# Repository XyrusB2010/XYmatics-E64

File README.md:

# XYmatics E64
XYmatics E64 (Engine, 64-bit) is a 5-axis Klipper mainboard, powered by a Raspberry Pi CM4 and STM32F407. It was originally built for <a href='https://github.com/XyrusB2010/XYmatics-Alpha/tree/main'>XYmatics Alpha</a>, but you can also use it for most 3D Printers.

## E64 Features
- Powered by STM32F407VET6 (MCU) and Raspberry Pi CM4 (Host)
- 1 USB-micro OTG port + 2 USB-A ports + 1 USB JST breakout, 100 Mbit RJ45 Socket for LAN, Micro SD card for extra storage
- 5 TMC2209 Stepsticks to drive stepper motors
- 3 Endstops/Switches
- 5 Controllable fans on base board + 1 for Raspberry Pi
- 8 CAN FD bus ports to reduce amount of cables
- CSI for camera input
- HDMI or DSI for display output
- I2C bus broken out

## E64 PCB

# XYmatics X42
XYmatics X42 (Xpansion, for 42mm motors) is a Klipper expansion board, designed to mount onto 42mm stepper motors. Powered by a STM32G0B1, it communicates to the E64 mainboard through CAN FD. This board simplifies the mainboard, and reduces the amount of cables going out. The X42 can also be used with most other 3D Printers.

## X42 Features
- Powered by STM32G0B1CBT6
- Supports Laser engravers, CNC routers and FDM extruders
- TJA1051T CAN FD module to communicate with E64
- ~~BLTouch compatible~~
- Two PWM controllable fans
- ADXL345 accelerometer included
- ~~3~~ 1 Endstop/Switch
- I2C bus ~~and neopixel~~ broken out
>  [!NOTE]
>  May re-add these removed features in future if possible.

## X42 PCB

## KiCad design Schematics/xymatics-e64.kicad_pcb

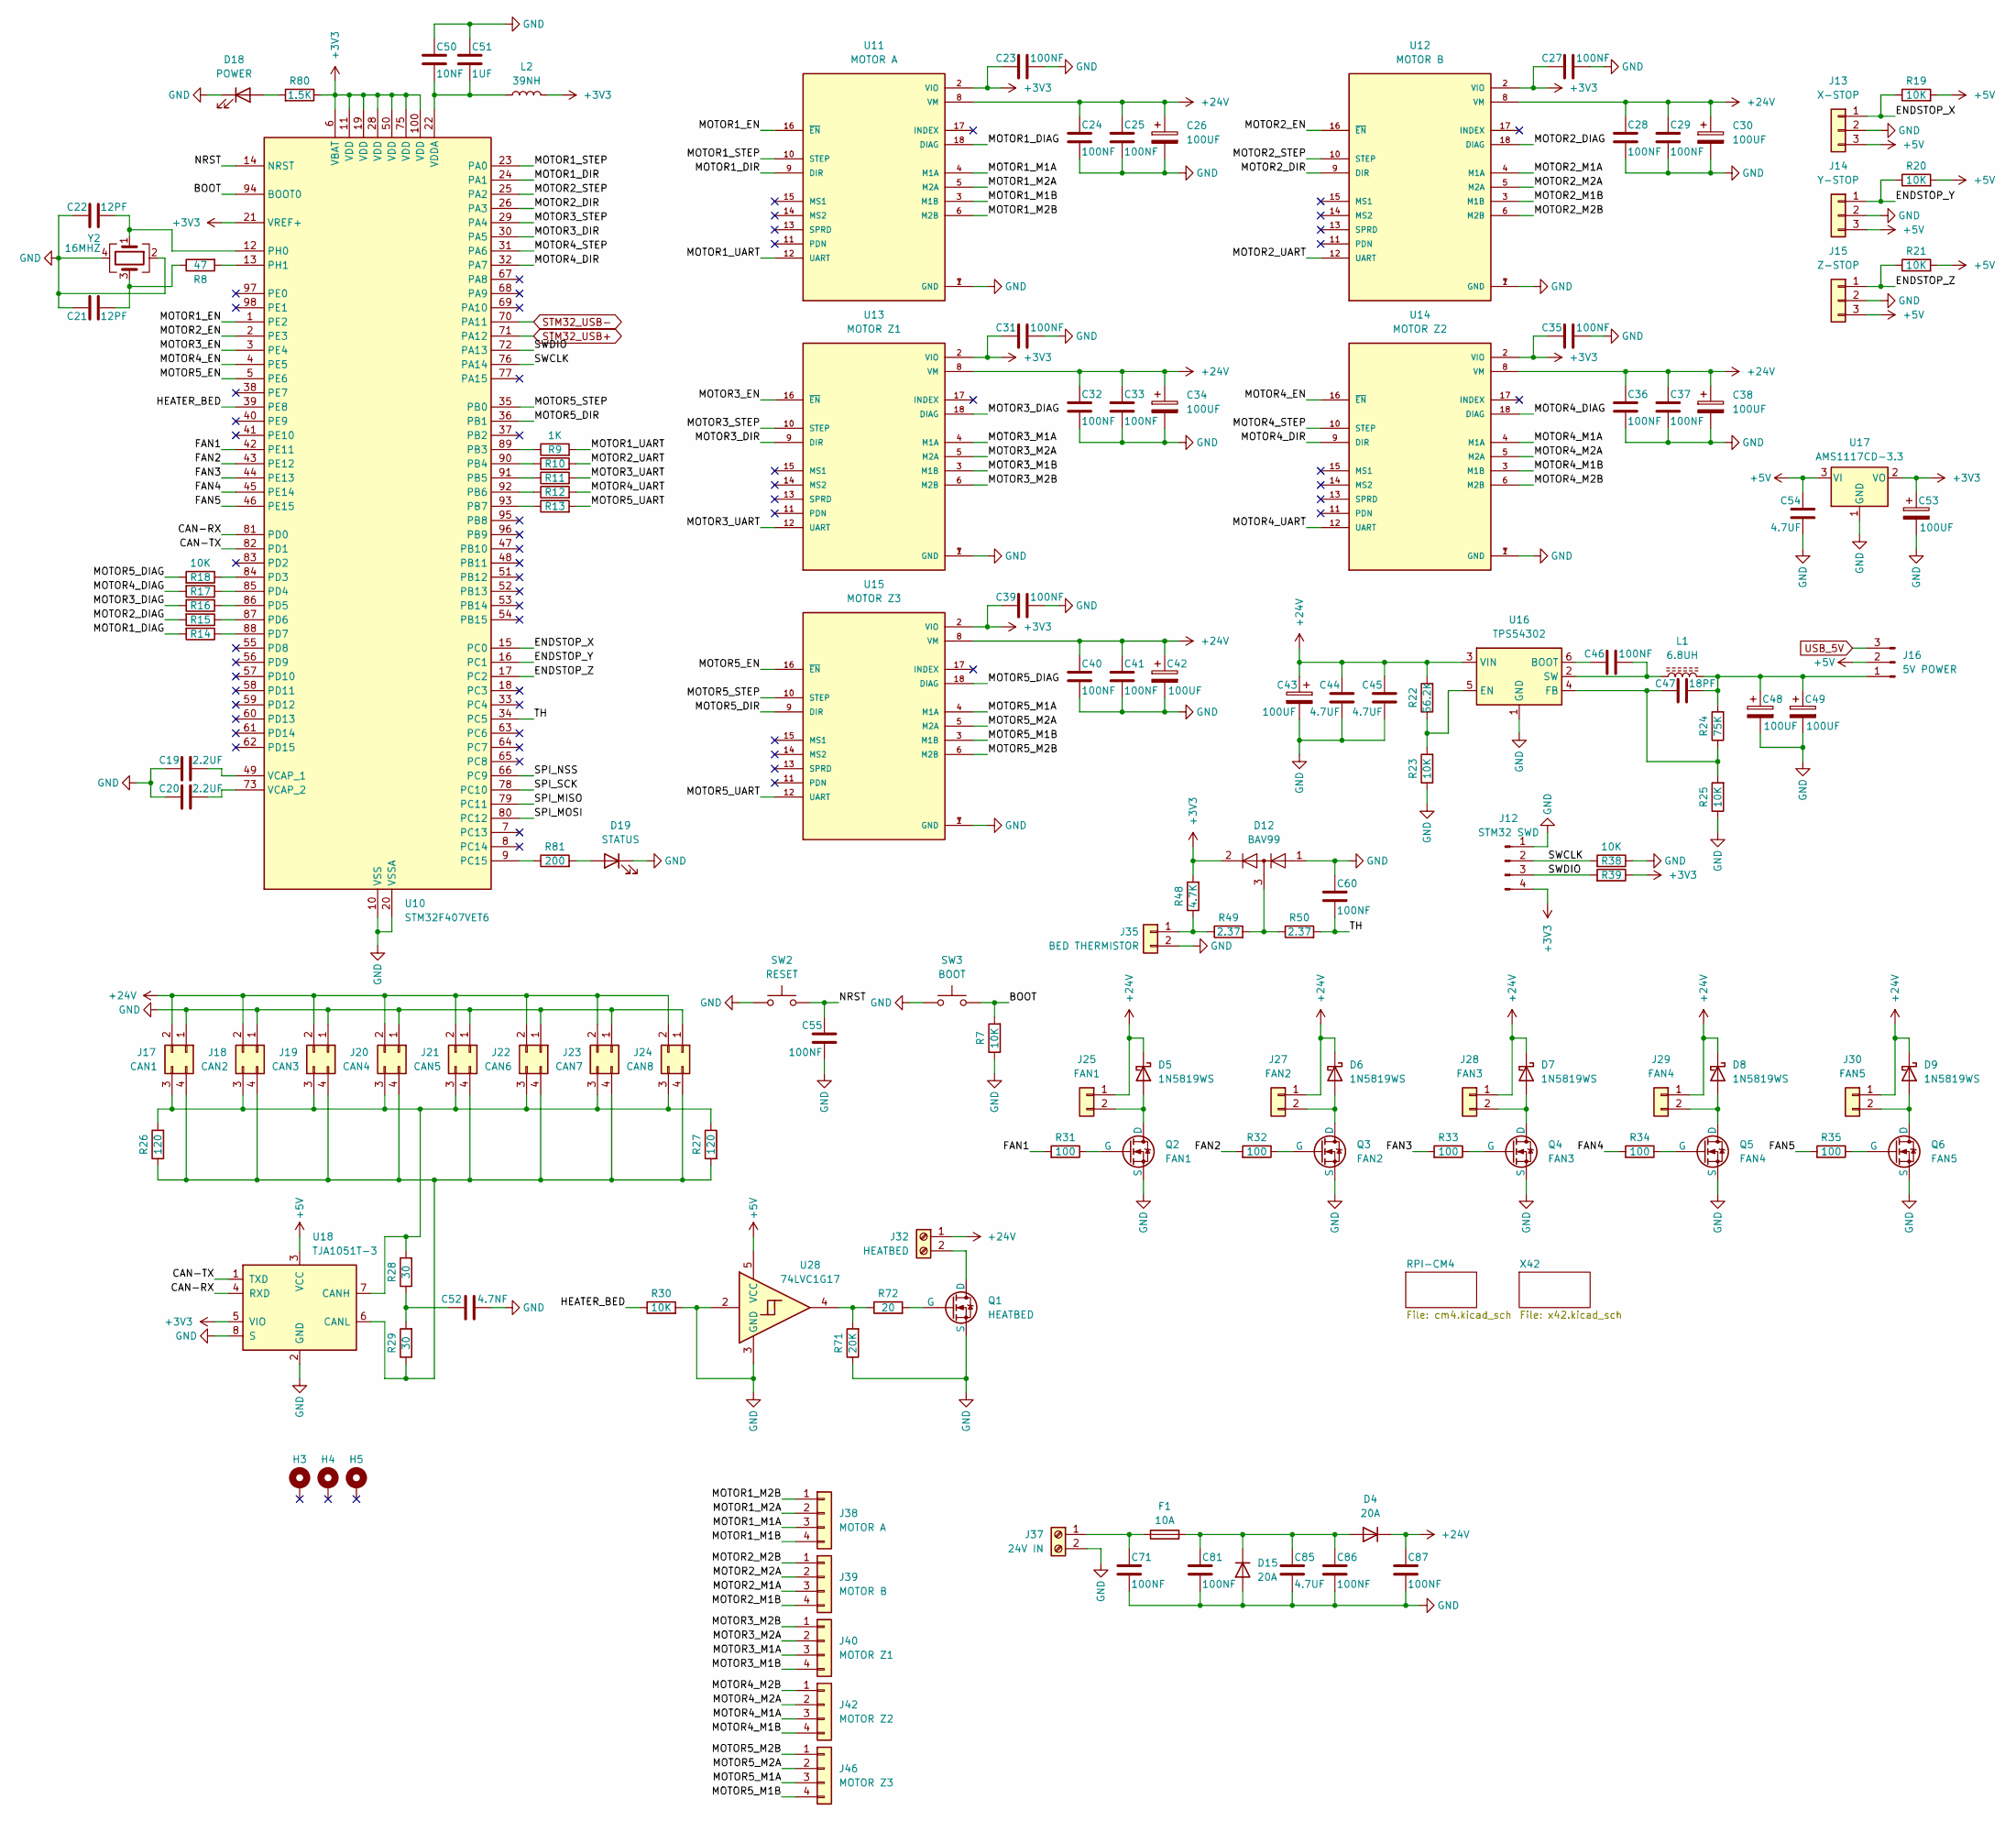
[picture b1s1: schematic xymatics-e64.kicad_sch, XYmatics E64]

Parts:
C19, C20: 2.2UF; C_0805_2012Metric
C21, C22: 12PF; C_0805_2012Metric
C23, C24, C25, C27, C28, C29, C31, C32, C33, C35, C36, C37, C39, C40, C41, C46, C55, C60, C71, C81, C86, C87: 100NF; C_0805_2012Metric
C26, C30, C34, C38, C42, C43, C48, C49, C53: 100UF; CP_Elec_5x3
C44, C45, C54, C85: 4.7UF; C_0805_2012Metric
C47: 18PF; C_0805_2012Metric
C50: 10NF; C_0805_2012Metric
C51: 1UF; C_0805_2012Metric
C52: 4.7NF; C_0805_2012Metric
D4, D15: 20A; D_SMB
D5, D6, D7, D8, D9: 1N5819WS; D_SOD-323
D12: BAV99; SOT-23
D18: POWER; LED_0805_2012Metric
D19: STATUS; LED_0805_2012Metric
F1: 10A; Fuse_Blade_ATO_directSolder
H3, H4, H5: MountingHole_Pad; MountingHole_3mm_Pad
J12: STM32 SWD; PinHeader_1x04_P2.54mm_Vertical
J13: X-STOP; JST_XH_B3B-XH-A_1x03_P2.50mm_Vertical
J14: Y-STOP; JST_XH_B3B-XH-A_1x03_P2.50mm_Vertical
J15: Z-STOP; JST_XH_B3B-XH-A_1x03_P2.50mm_Vertical
J16: 5V POWER; PinHeader_1x03_P2.54mm_Vertical
J17: CAN1; Molex_Micro-Fit_3.0_43045-0412_2x02_P3.00mm_Vertical
J18: CAN2; Molex_Micro-Fit_3.0_43045-0412_2x02_P3.00mm_Vertical
J19: CAN3; Molex_Micro-Fit_3.0_43045-0412_2x02_P3.00mm_Vertical
J20: CAN4; Molex_Micro-Fit_3.0_43045-0412_2x02_P3.00mm_Vertical
J21: CAN5; Molex_Micro-Fit_3.0_43045-0412_2x02_P3.00mm_Vertical
J22: CAN6; Molex_Micro-Fit_3.0_43045-0412_2x02_P3.00mm_Vertical
J23: CAN7; Molex_Micro-Fit_3.0_43045-0412_2x02_P3.00mm_Vertical
J24: CAN8; Molex_Micro-Fit_3.0_43045-0412_2x02_P3.00mm_Vertical
J25: FAN1; JST_XH_B2B-XH-A_1x02_P2.50mm_Vertical
J27: FAN2; JST_XH_B2B-XH-A_1x02_P2.50mm_Vertical
J28: FAN3; JST_XH_B2B-XH-A_1x02_P2.50mm_Vertical
J29: FAN4; JST_XH_B2B-XH-A_1x02_P2.50mm_Vertical
J30: FAN5; JST_XH_B2B-XH-A_1x02_P2.50mm_Vertical
J32: HEATBED; TerminalBlock_MaiXu_MX126-5.0-02P_1x02_P5.00mm
J35: BED THERMISTOR; JST_XH_B2B-XH-A_1x02_P2.50mm_Vertical
J37: 24V IN; TerminalBlock_MaiXu_MX126-5.0-02P_1x02_P5.00mm
J38: MOTOR A; JST_XH_B4B-XH-A_1x04_P2.50mm_Vertical
J39: MOTOR B; JST_XH_B4B-XH-A_1x04_P2.50mm_Vertical
J40: MOTOR Z1; JST_XH_B4B-XH-A_1x04_P2.50mm_Vertical
J42: MOTOR Z2; JST_XH_B4B-XH-A_1x04_P2.50mm_Vertical
J46: MOTOR Z3; JST_XH_B4B-XH-A_1x04_P2.50mm_Vertical
L1: 6.8UH; L_6.3x6.3_H3
L2: 39NH; L_0805_2012Metric
Q1: HEATBED; TO-252-2
Q2: FAN1; SOT-23
Q3: FAN2; SOT-23
Q4: FAN3; SOT-23
Q5: FAN4; SOT-23
Q6: FAN5; SOT-23
R7, R14, R15, R16, R17, R18, R19, R20, R21, R23, R25, R30, R38, R39: 10K; R_0805_2012Metric
R8: 47; R_0805_2012Metric
R9, R10, R11, R12, R13: 1K; R_0805_2012Metric
R22: 56.2K; R_1206_3216Metric
R24: 75K; R_1206_3216Metric
R26, R27: 120; R_0805_2012Metric
R28, R29: 30; R_0805_2012Metric
R31, R32, R33, R34, R35: 100; R_0805_2012Metric
R48: 4.7K; R_0805_2012Metric
R49, R50: 2.37; R_0805_2012Metric
R71: 20K; R_0805_2012Metric
R72: 20; R_0805_2012Metric
R80: 1.5K; R_0805_2012Metric
R81: 200; R_0805_2012Metric
SW2: RESET; SW_Tactile_SPST_NO_Straight_CK_PTS636Sx25SMTRLFS
SW3: BOOT; SW_Tactile_SPST_NO_Straight_CK_PTS636Sx25SMTRLFS
U10: STM32F407VET6; LQFP-100_14x14mm_P0.5mm
U11: MOTOR A; MODULE_TMC2209_SILENTSTEPSTICK; PARTREV 1.20
U12: MOTOR B; MODULE_TMC2209_SILENTSTEPSTICK; PARTREV 1.20
U13: MOTOR Z1; MODULE_TMC2209_SILENTSTEPSTICK; PARTREV 1.20
U14: MOTOR Z2; MODULE_TMC2209_SILENTSTEPSTICK; PARTREV 1.20
U15: MOTOR Z3; MODULE_TMC2209_SILENTSTEPSTICK; PARTREV 1.20
U16: TPS54302; SOT-23-6
U17: AMS1117CD-3.3; TO-252-2
U18: TJA1051T-3; SOIC-8_3.9x4.9mm_P1.27mm
U28: 74LVC1G17; SOT-23-5
Y2: 16MHZ; Crystal_SMD_Abracon_ABM3B-4Pin_5.0x3.2mm

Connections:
+3V3: C23.2, C27.2, C31.2, C35.2, C39.2, C53.1, D12.2 (A), J12.4, L2.2, R39.1, R48.2, R80.1, U10.6 (VBAT), U10.11 (VDD), U10.19 (VDD), U10.21 (VREF+), U10.28 (VDD), U10.50 (VDD), U10.75 (VDD), U10.100 (VDD), U11.2 (VIO), U12.2 (VIO), U13.2 (VIO), U14.2 (VIO), U15.2 (VIO), U17.2 (VO), U18.5 (VIO)
+5V: C54.1, J13.3, J14.3, J15.3, J16.2, R19.2, R20.2, R21.2, U17.3 (VI), U18.3 (VCC), U28.5 (VCC); also elsewhere on the board
+24V: C24.1, C25.1, C26.1, C28.1, C29.1, C30.1, C32.1, C33.1, C34.1, C36.1, C37.1, C38.1, C40.1, C41.1, C42.1, C43.1, C44.1, C45.1, C87.1, D4.1 (K), D5.1 (K), D6.1 (K), D7.1 (K), D8.1 (K), D9.1 (K), J17.2, J18.2, J19.2, J20.2, J21.2, J22.2, J23.2, J24.2, J25.1, J27.1, J28.1, J29.1, J30.1, J32.1, R22.2, U11.8 (VM), U12.8 (VM), U13.8 (VM), U14.8 (VM), U15.8 (VM), U16.3 (VIN)
/BOOT: R7.2, SW3.2, U10.94 (BOOT0)
/CAN-RX: U10.81 (PD0), U18.4 (RXD)
/CAN-TX: U10.82 (PD1), U18.1 (TXD)
/ENDSTOP_X: J13.1, R19.1, U10.15 (PC0)
/ENDSTOP_Y: J14.1, R20.1, U10.16 (PC1)
/ENDSTOP_Z: J15.1, R21.1, U10.17 (PC2)
/FAN1: R31.2, U10.42 (PE11)
/FAN2: R32.2, U10.43 (PE12)
/FAN3: R33.2, U10.44 (PE13)
/FAN4: R34.2, U10.45 (PE14)
/FAN5: R35.2, U10.46 (PE15)
/HEATER_BED: R30.1, U10.39 (PE8)
/MOTOR1_DIAG: R14.2, U11.18 (DIAG)
/MOTOR1_DIR: U10.24 (PA1), U11.9 (DIR)
/MOTOR1_EN: U10.1 (PE2), U11.16 (~EN)
/MOTOR1_M1A: J38.3, U11.4 (M1A)
/MOTOR1_M1B: J38.4, U11.3 (M1B)
/MOTOR1_M2A: J38.2, U11.5 (M2A)
/MOTOR1_M2B: J38.1, U11.6 (M2B)
/MOTOR1_STEP: U10.23 (PA0), U11.10 (STEP)
/MOTOR1_UART: R9.2, U11.12 (UART)
/MOTOR2_DIAG: R15.2, U12.18 (DIAG)
/MOTOR2_DIR: U10.26 (PA3), U12.9 (DIR)
/MOTOR2_EN: U10.2 (PE3), U12.16 (~EN)
/MOTOR2_M1A: J39.3, U12.4 (M1A)
/MOTOR2_M1B: J39.4, U12.3 (M1B)
/MOTOR2_M2A: J39.2, U12.5 (M2A)
/MOTOR2_M2B: J39.1, U12.6 (M2B)
/MOTOR2_STEP: U10.25 (PA2), U12.10 (STEP)
/MOTOR2_UART: R10.2, U12.12 (UART)
/MOTOR3_DIAG: R16.2, U13.18 (DIAG)
/MOTOR3_DIR: U10.30 (PA5), U13.9 (DIR)
/MOTOR3_EN: U10.3 (PE4), U13.16 (~EN)
/MOTOR3_M1A: J40.3, U13.4 (M1A)
/MOTOR3_M1B: J40.4, U13.3 (M1B)
/MOTOR3_M2A: J40.2, U13.5 (M2A)
/MOTOR3_M2B: J40.1, U13.6 (M2B)
/MOTOR3_STEP: U10.29 (PA4), U13.10 (STEP)
/MOTOR3_UART: R11.2, U13.12 (UART)
/MOTOR4_DIAG: R17.2, U14.18 (DIAG)
/MOTOR4_DIR: U10.32 (PA7), U14.9 (DIR)
/MOTOR4_EN: U10.4 (PE5), U14.16 (~EN)
/MOTOR4_M1A: J42.3, U14.4 (M1A)
/MOTOR4_M1B: J42.4, U14.3 (M1B)
/MOTOR4_M2A: J42.2, U14.5 (M2A)
/MOTOR4_M2B: J42.1, U14.6 (M2B)
/MOTOR4_STEP: U10.31 (PA6), U14.10 (STEP)
/MOTOR4_UART: R12.2, U14.12 (UART)
/MOTOR5_DIAG: R18.2, U15.18 (DIAG)
/MOTOR5_DIR: U10.36 (PB1), U15.9 (DIR)
/MOTOR5_EN: U10.5 (PE6), U15.16 (~EN)
/MOTOR5_M1A: J46.3, U15.4 (M1A)
/MOTOR5_M1B: J46.4, U15.3 (M1B)
/MOTOR5_M2A: J46.2, U15.5 (M2A)
/MOTOR5_M2B: J46.1, U15.6 (M2B)
/MOTOR5_STEP: U10.35 (PB0), U15.10 (STEP)
/MOTOR5_UART: R13.2, U15.12 (UART)
/NRST: C55.1, SW2.2, U10.14 (NRST)
/SPI_MISO: U10.79 (PC11)
/SPI_MOSI: U10.80 (PC12)
/SPI_NSS: U10.66 (PC9)
/SPI_SCK: U10.78 (PC10)
/SWCLK: J12.2, R38.2, U10.76 (PA14)
/SWDIO: J12.3, R39.2, U10.72 (PA13)
/TH: C60.2, R50.2, U10.34 (PC5)
GND: C19.2, C20.2, C21.1, C22.1, C23.1, C24.2, C25.2, C26.2, C27.1, C28.2, C29.2, C30.2, C31.1, C32.2, C33.2, C34.2, C35.1, C36.2, C37.2, C38.2, C39.1, C40.2, C41.2, C42.2, C43.2, C44.2, C45.2, C48.2, C49.2, C50.1, C51.1, C52.2, C53.2, C54.2, C55.2, C60.1, C71.2, C81.2, C85.2, C86.2, C87.2, D12.1 (K), D15.2 (A), D18.1 (K), D19.1 (K), J12.1, J13.2, J14.2, J15.2, J17.1, J18.1, J19.1, J20.1, J21.1, J22.1, J23.1, J24.1, J35.2, J37.2, Q1.3 (S), Q2.3 (S), Q3.3 (S), Q4.3 (S), Q5.3 (S), Q6.3 (S), R7.1, R23.1, R25.1, R30.2, R38.1, R71.1, SW2.1, SW3.1, U10.10 (VSS), U10.20 (VSSA), U10.27 (VSS), U10.74 (VSS), U10.99 (VSS), U11.1 (GND), U11.7 (GND), U12.1 (GND), U12.7 (GND), U13.1 (GND), U13.7 (GND), U14.1 (GND), U14.7 (GND), U15.1 (GND), U15.7 (GND), U16.1 (GND), U17.1 (GND), U18.2 (GND), U18.8 (S), U28.2, U28.3 (GND), Y2.2, Y2.4; also elsewhere on the board
unnamed: C21.2, R8.1, Y2.3
unnamed: C52.1, R28.1, R29.2
unnamed: D5.2 (A), J25.2, Q2.1 (D)
unnamed: D6.2 (A), J27.2, Q3.1 (D)
unnamed: D7.2 (A), J28.2, Q4.1 (D)
unnamed: D8.2 (A), J29.2, Q5.1 (D)
unnamed: D9.2 (A), J30.2, Q6.1 (D)
unnamed: D12.3 (K), R49.2, R50.1
unnamed: C81.1, C85.1, C86.1, D4.2 (A), D15.1 (K), F1.2
unnamed: D18.2 (A), R80.2
unnamed: D19.2 (A), R81.2
unnamed: C47.1, C48.1, C49.1, J16.1, L1.2, R24.2
unnamed: J17.3, J18.3, J19.3, J20.3, J21.3, J22.3, J23.3, J24.3, R26.2, R27.1, R28.2, U18.7 (CANH)
unnamed: J17.4, J18.4, J19.4, J20.4, J21.4, J22.4, J23.4, J24.4, R26.1, R27.2, R29.1, U18.6 (CANL)
unnamed: J32.2, Q1.2 (D)
unnamed: J35.1, R48.1, R49.1
unnamed: C71.1, F1.1, J37.1
unnamed: Q1.1 (G), R72.2
unnamed: Q2.2 (G), R31.1
unnamed: Q3.2 (G), R32.1
unnamed: Q4.2 (G), R33.1
unnamed: Q5.2 (G), R34.1
unnamed: Q6.2 (G), R35.1
unnamed: R71.2, R72.1, U28.4
unnamed: R9.1, U10.89 (PB3)
unnamed: R10.1, U10.90 (PB4)
unnamed: R11.1, U10.91 (PB5)
unnamed: R12.1, U10.92 (PB6)
unnamed: R13.1, U10.93 (PB7)
unnamed: R81.1, U10.9 (PC15)
unnamed: R18.1, U10.84 (PD3)
unnamed: R17.1, U10.85 (PD4)
unnamed: R16.1, U10.86 (PD5)
unnamed: R15.1, U10.87 (PD6)
unnamed: R14.1, U10.88 (PD7)
unnamed: C22.2, U10.12 (PH0), Y2.1
unnamed: R8.2, U10.13 (PH1)
unnamed: C19.1, U10.49 (VCAP_1)
unnamed: C20.1, U10.73 (VCAP_2)
unnamed: C50.2, C51.2, L2.1, U10.22 (VDDA)
unnamed: C46.2, U16.6 (BOOT)
unnamed: R22.1, R23.2, U16.5 (EN)
unnamed: C47.2, R24.1, R25.2, U16.4 (FB)
unnamed: C46.1, L1.1, U16.2 (SW)
STM32_USB+: U10.71 (PA12); also elsewhere on the board
STM32_USB-: U10.70 (PA11); also elsewhere on the board
USB_5V: J16.3; also elsewhere on the board

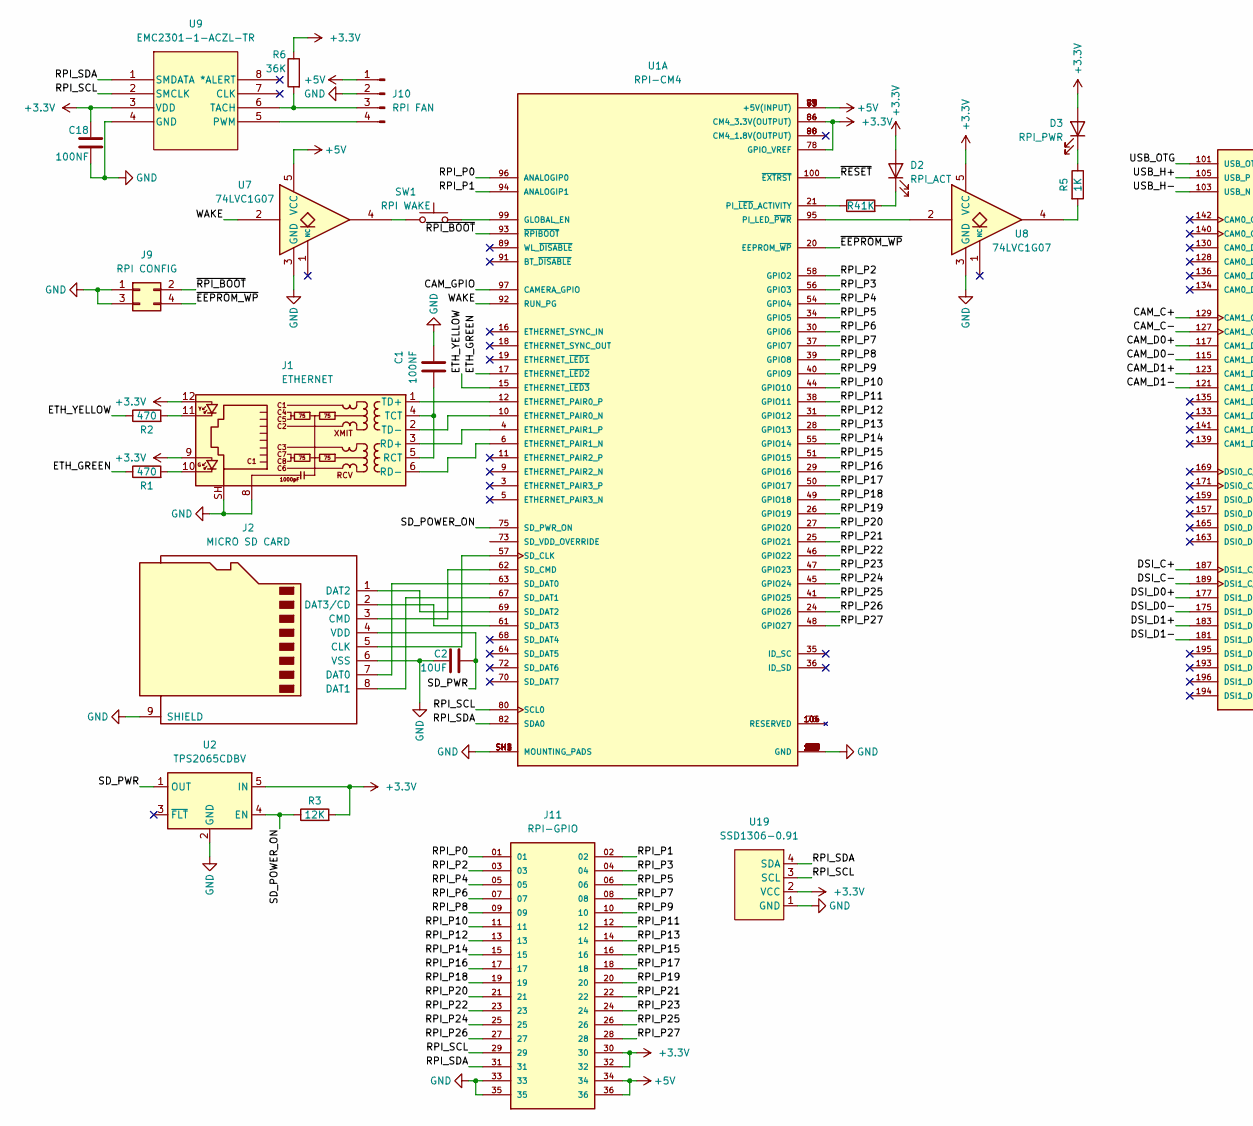
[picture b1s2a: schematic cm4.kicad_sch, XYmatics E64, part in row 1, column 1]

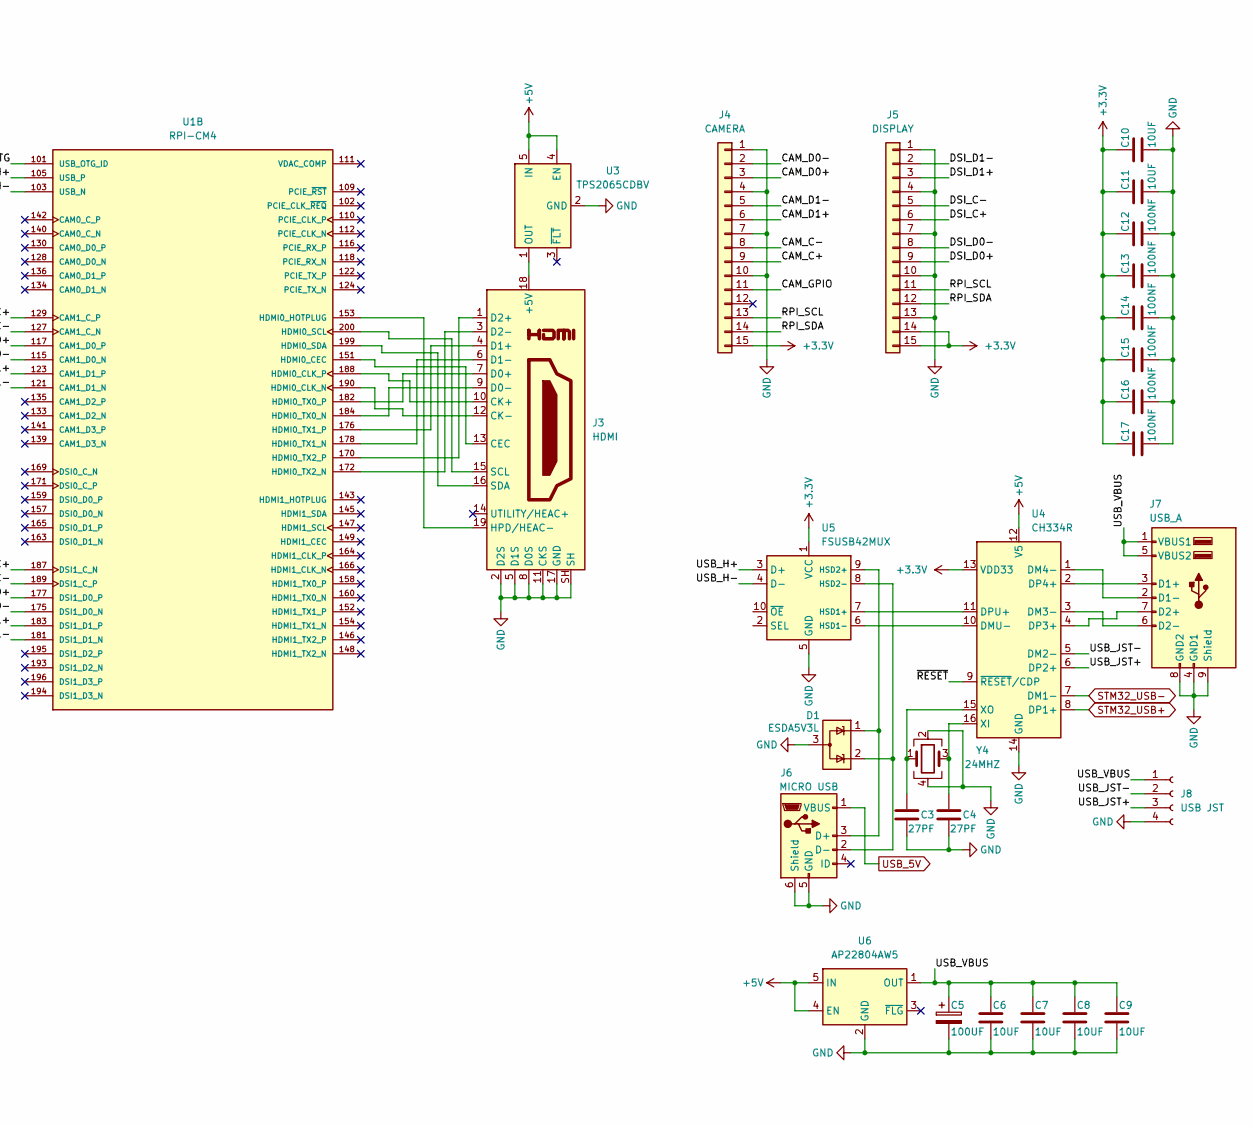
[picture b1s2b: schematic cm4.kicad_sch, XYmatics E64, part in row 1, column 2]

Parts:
C1, C12, C13, C14, C15, C16, C17, C18: 100NF; C_0805_2012Metric
C2, C6, C7, C8, C9, C10, C11: 10UF; C_0805_2012Metric
C3, C4: 27PF; C_0805_2012Metric
C5: 100UF; CP_Elec_5x3
D1: ESDA5V3L; SOT-23-3
D2: RPI_ACT; LED_0805_2012Metric
D3: RPI_PWR; LED_0805_2012Metric
J1: ETHERNET; RJ45_Hanrun_HR911105A_Horizontal
J2: MICRO SD CARD; microSD_HC_Wuerth_693072010801
J3: HDMI; HDMI_A_Molex_208658-1001_Horizontal
J4: CAMERA; Molex_502231-1500_1x15-1SH_P0.5mm_Vertical
J5: DISPLAY; Molex_502231-1500_1x15-1SH_P0.5mm_Vertical
J6: MICRO USB; USB_Micro-B_Molex_47346-0001
J7: USB_A; USB_A_CUI_UJ2-ADH-TH_Horizontal_Stacked
J8: USB JST; JST_XH_B4B-XH-A_1x04_P2.50mm_Vertical
J9: RPI CONFIG; PinHeader_2x02_P2.54mm_Vertical
J10: RPI FAN; PinHeader_1x04_P2.54mm_Vertical
J11: RPI-GPIO; SAMTEC_TST-118-01-T-D; PARTREV R
R1, R2: 470; R_0805_2012Metric
R3: 12K; R_0805_2012Metric
R4, R5: 1K; R_0805_2012Metric
R6: 36K; R_0805_2012Metric
SW1: RPI WAKE; SW_Tactile_SPST_NO_Straight_CK_PTS636Sx25SMTRLFS
U1: RPI-CM4; MODULE_CM4102008; PARTREV 2021-10-12
U2, U3: TPS2065CDBV; SOT-23-5
U4: CH334R; QSOP-16_3.9x4.9mm_P0.635mm
U5: FSUSB42MUX; MSOP-10_3x3mm_P0.5mm
U6: AP22804AW5; SOT-23-5
U7, U8: 74LVC1G07; SOT-23-5
U9: EMC2301-1-ACZL-TR; MSOP8_MC_MCH
U19: SSD1306-0.91; OLED-12832
Y4: 24MHZ; Crystal_SMD_Abracon_ABM3B-4Pin_5.0x3.2mm

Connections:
+3.3V: C10.1, C11.1, C12.1, C13.1, C14.1, C15.1, C16.1, C17.1, C18.1, D2.2 (A), D3.2 (A), J1.9, J1.12, J4.15, J5.14, J5.15, J11.30, J11.32, R3.2, R6.1, U1.78 (GPIO_VREF), U1.84 (CM4_3.3V(OUTPUT)), U1.86 (CM4_3.3V(OUTPUT)), U2.5 (IN), U4.13 (VDD33), U5.1 (VCC), U8.5 (VCC), U9.3 (VDD), U19.2 (VCC)
+5V: J10.1, J11.34, J11.36, U1.77 (+5V(INPUT)), U1.79 (+5V(INPUT)), U1.81 (+5V(INPUT)), U1.83 (+5V(INPUT)), U1.85 (+5V(INPUT)), U1.87 (+5V(INPUT)), U3.4 (EN), U3.5 (IN), U4.12 (V5), U6.4 (EN), U6.5 (IN), U7.5 (VCC); also elsewhere on the board
/RPI-CM4/CAM_C+: J4.9, U1.129 (CAM1_C_P)
/RPI-CM4/CAM_C-: J4.8, U1.127 (CAM1_C_N)
/RPI-CM4/CAM_D0+: J4.3, U1.117 (CAM1_D0_P)
/RPI-CM4/CAM_D0-: J4.2, U1.115 (CAM1_D0_N)
/RPI-CM4/CAM_D1+: J4.6, U1.123 (CAM1_D1_P)
/RPI-CM4/CAM_D1-: J4.5, U1.121 (CAM1_D1_N)
/RPI-CM4/CAM_GPIO: J4.11, U1.97 (CAMERA_GPIO)
/RPI-CM4/DSI_C+: J5.6, U1.187 (DSI1_C_N)
/RPI-CM4/DSI_C-: J5.5, U1.189 (DSI1_C_P)
/RPI-CM4/DSI_D0+: J5.9, U1.177 (DSI1_D0_P)
/RPI-CM4/DSI_D0-: J5.8, U1.175 (DSI1_D0_N)
/RPI-CM4/DSI_D1+: J5.3, U1.183 (DSI1_D1_P)
/RPI-CM4/DSI_D1-: J5.2, U1.181 (DSI1_D1_N)
/RPI-CM4/ETH_GREEN: R1.1, U1.17 (ETHERNET_~LED2)
/RPI-CM4/ETH_YELLOW: R2.1, U1.15 (ETHERNET_~LED3)
/RPI-CM4/RPI_P0: J11.01, U1.96 (ANALOGIP0)
/RPI-CM4/RPI_P1: J11.02, U1.94 (ANALOGIP1)
/RPI-CM4/RPI_P2: J11.03, U1.58 (GPIO2)
/RPI-CM4/RPI_P3: J11.04, U1.56 (GPIO3)
/RPI-CM4/RPI_P4: J11.05, U1.54 (GPIO4)
/RPI-CM4/RPI_P5: J11.06, U1.34 (GPIO5)
/RPI-CM4/RPI_P6: J11.07, U1.30 (GPIO6)
/RPI-CM4/RPI_P7: J11.08, U1.37 (GPIO7)
/RPI-CM4/RPI_P8: J11.09, U1.39 (GPIO8)
/RPI-CM4/RPI_P9: J11.10, U1.40 (GPIO9)
/RPI-CM4/RPI_P10: J11.11, U1.44 (GPIO10)
/RPI-CM4/RPI_P11: J11.12, U1.38 (GPIO11)
/RPI-CM4/RPI_P12: J11.13, U1.31 (GPIO12)
/RPI-CM4/RPI_P13: J11.14, U1.28 (GPIO13)
/RPI-CM4/RPI_P14: J11.15, U1.55 (GPIO14)
/RPI-CM4/RPI_P15: J11.16, U1.51 (GPIO15)
/RPI-CM4/RPI_P16: J11.17, U1.29 (GPIO16)
/RPI-CM4/RPI_P17: J11.18, U1.50 (GPIO17)
/RPI-CM4/RPI_P18: J11.19, U1.49 (GPIO18)
/RPI-CM4/RPI_P19: J11.20, U1.26 (GPIO19)
/RPI-CM4/RPI_P20: J11.21, U1.27 (GPIO20)
/RPI-CM4/RPI_P21: J11.22, U1.25 (GPIO21)
/RPI-CM4/RPI_P22: J11.23, U1.46 (GPIO22)
/RPI-CM4/RPI_P23: J11.24, U1.47 (GPIO23)
/RPI-CM4/RPI_P24: J11.25, U1.45 (GPIO24)
/RPI-CM4/RPI_P25: J11.26, U1.41 (GPIO25)
/RPI-CM4/RPI_P26: J11.27, U1.24 (GPIO26)
/RPI-CM4/RPI_P27: J11.28, U1.48 (GPIO27)
/RPI-CM4/RPI_SCL: J4.13, J5.11, J11.29, U1.80 (SCL0), U9.2 (SMCLK), U19.3 (SCL)
/RPI-CM4/RPI_SDA: J4.14, J5.12, J11.31, U1.82 (SDA0), U9.1 (SMDATA), U19.4 (SDA)
/RPI-CM4/SD_POWER_ON: R3.1, U1.75 (SD_PWR_ON), U2.4 (EN)
/RPI-CM4/SD_PWR: C2.1, J2.4 (VDD), U2.1 (OUT)
/RPI-CM4/USB_H+: U1.105 (USB_P), U5.3 (D+)
/RPI-CM4/USB_H-: U1.103 (USB_N), U5.4 (D-)
/RPI-CM4/USB_JST+: J8.3, U4.6 (DP2+)
/RPI-CM4/USB_JST-: J8.2, U4.5 (DM2-)
/RPI-CM4/USB_OTG: U1.101 (USB_OTG_ID)
/RPI-CM4/USB_VBUS: C5.1, C6.1, C7.1, C8.1, C9.1, J7.1 (VBUS1), J7.5 (VBUS2), J8.1, U6.1 (OUT)
/RPI-CM4/WAKE: U1.92 (RUN_PG), U7.2
/RPI-CM4/~EEPROM_WP: J9.4, U1.20 (EEPROM_~WP)
/RPI-CM4/~RESET: U1.100 (~EXTRST), U4.9 (~RESET/CDP)
/RPI-CM4/~RPI_BOOT: J9.2, U1.93 (~RPIBOOT)
GND: C1.1, C2.2, C3.2, C4.2, C5.2, C6.2, C7.2, C8.2, C9.2, C10.2, C11.2, C12.2, C13.2, C14.2, C15.2, C16.2, C17.2, C18.2, D1.3 (A), J1.8, J1.SH, J2.6 (VSS), J2.9 (SHIELD), J3.2 (D2S), J3.5 (D1S), J3.8 (D0S), J3.11 (CKS), J3.17 (GND), J3.SH, J4.1, J4.4, J4.7, J4.10, J5.1, J5.4, J5.7, J5.10, J5.13, J6.5 (GND), J6.6 (Shield), J7.4 (GND1), J7.8 (GND2), J7.9 (Shield), J8.4, J9.1, J9.3, J10.2, J11.33, J11.35, U1.1 (GND), U1.2 (GND), U1.7 (GND), U1.8 (GND), U1.13 (GND), U1.14 (GND), U1.22 (GND), U1.23 (GND), U1.32 (GND), U1.33 (GND), U1.42 (GND), U1.43 (GND), U1.52 (GND), U1.53 (GND), U1.59 (GND), U1.60 (GND), U1.65 (GND), U1.66 (GND), U1.71 (GND), U1.74 (GND), U1.98 (GND), U1.107 (GND), U1.108 (GND), U1.113 (GND), U1.114 (GND), U1.119 (GND), U1.120 (GND), U1.125 (GND), U1.126 (GND), U1.131 (GND), U1.132 (GND), U1.137 (GND), U1.138 (GND), U1.144 (GND), U1.150 (GND), U1.155 (GND), U1.156 (GND), U1.161 (GND), U1.162 (GND), U1.167 (GND), U1.168 (GND), U1.173 (GND), U1.174 (GND), U1.179 (GND), U1.180 (GND), U1.185 (GND), U1.186 (GND), U1.191 (GND), U1.192 (GND), U1.197 (GND), U1.198 (GND), U1.SH1 (MOUNTING_PADS), U1.SH2 (MOUNTING_PADS), U1.SH3 (MOUNTING_PADS), U1.SH4 (MOUNTING_PADS), U2.2 (GND), U3.2 (GND), U4.14 (GND), U5.5 (GND), U6.2 (GND), U7.3 (GND), U8.3 (GND), U9.4 (GND), U19.1 (GND), Y4.2, Y4.4; also elsewhere on the board
unnamed: D2.1 (K), R4.2
unnamed: D3.1 (K), R5.1
unnamed: J1.10, R1.2
unnamed: J1.11, R2.2
unnamed: C1.2, J1.4 (TCT), J1.5 (RCT)
unnamed: J1.3 (RD+), U1.4 (ETHERNET_PAIR1_P)
unnamed: J1.6 (RD-), U1.6 (ETHERNET_PAIR1_N)
unnamed: J1.1 (TD+), U1.12 (ETHERNET_PAIR0_P)
unnamed: J1.2 (TD-), U1.10 (ETHERNET_PAIR0_N)
unnamed: J2.5 (CLK), U1.57 (SD_CLK)
unnamed: J2.3 (CMD), U1.62 (SD_CMD)
unnamed: J2.7 (DAT0), U1.63 (SD_DAT0)
unnamed: J2.8 (DAT1), U1.67 (SD_DAT1)
unnamed: J2.1 (DAT2), U1.69 (SD_DAT2)
unnamed: J2.2 (DAT3/CD), U1.61 (SD_DAT3)
unnamed: J3.18 (+5V), U3.1 (OUT)
unnamed: J3.13 (CEC), U1.151 (HDMI0_CEC)
unnamed: J3.10 (CK+), U1.188 (HDMI0_CLK_P)
unnamed: J3.12 (CK-), U1.190 (HDMI0_CLK_N)
unnamed: J3.7 (D0+), U1.182 (HDMI0_TX0_P)
unnamed: J3.9 (D0-), U1.184 (HDMI0_TX0_N)
unnamed: J3.4 (D1+), U1.176 (HDMI0_TX1_P)
unnamed: J3.6 (D1-), U1.178 (HDMI0_TX1_N)
unnamed: J3.1 (D2+), U1.170 (HDMI0_TX2_P)
unnamed: J3.3 (D2-), U1.172 (HDMI0_TX2_N)
unnamed: J3.19 (HPD/HEAC-), U1.153 (HDMI0_HOTPLUG)
unnamed: J3.15 (SCL), U1.200 (HDMI0_SCL)
unnamed: J3.16 (SDA), U1.199 (HDMI0_SDA)
unnamed: D1.1 (K), J6.3 (D+), U5.9 (HSD2+)
unnamed: D1.2 (K), J6.2 (D-), U5.8 (HSD2-)
unnamed: J7.3 (D1+), U4.2 (DP4+)
unnamed: J7.2 (D1-), U4.1 (DM4-)
unnamed: J7.7 (D2+), U4.4 (DP3+)
unnamed: J7.6 (D2-), U4.3 (DM3-)
unnamed: J10.3, R6.2, U9.6 (TACH)
unnamed: J10.4, U9.5 (PWM)
unnamed: R5.2, U8.4
unnamed: SW1.2, U7.4
unnamed: SW1.1, U1.99 (GLOBAL_EN)
unnamed: U1.95 (PI_LED_~PWR), U8.2
unnamed: R4.1, U1.21 (PI_~LED_ACTIVITY)
unnamed: U4.10 (DMU-), U5.6 (HSD1-)
unnamed: U4.11 (DPU+), U5.7 (HSD1+)
unnamed: C4.1, U4.16 (XI), Y4.3
unnamed: C3.1, U4.15 (XO), Y4.1
STM32_USB+: U4.8 (DP1+); also elsewhere on the board
STM32_USB-: U4.7 (DM1-); also elsewhere on the board
USB_5V: J6.1 (VBUS); also elsewhere on the board

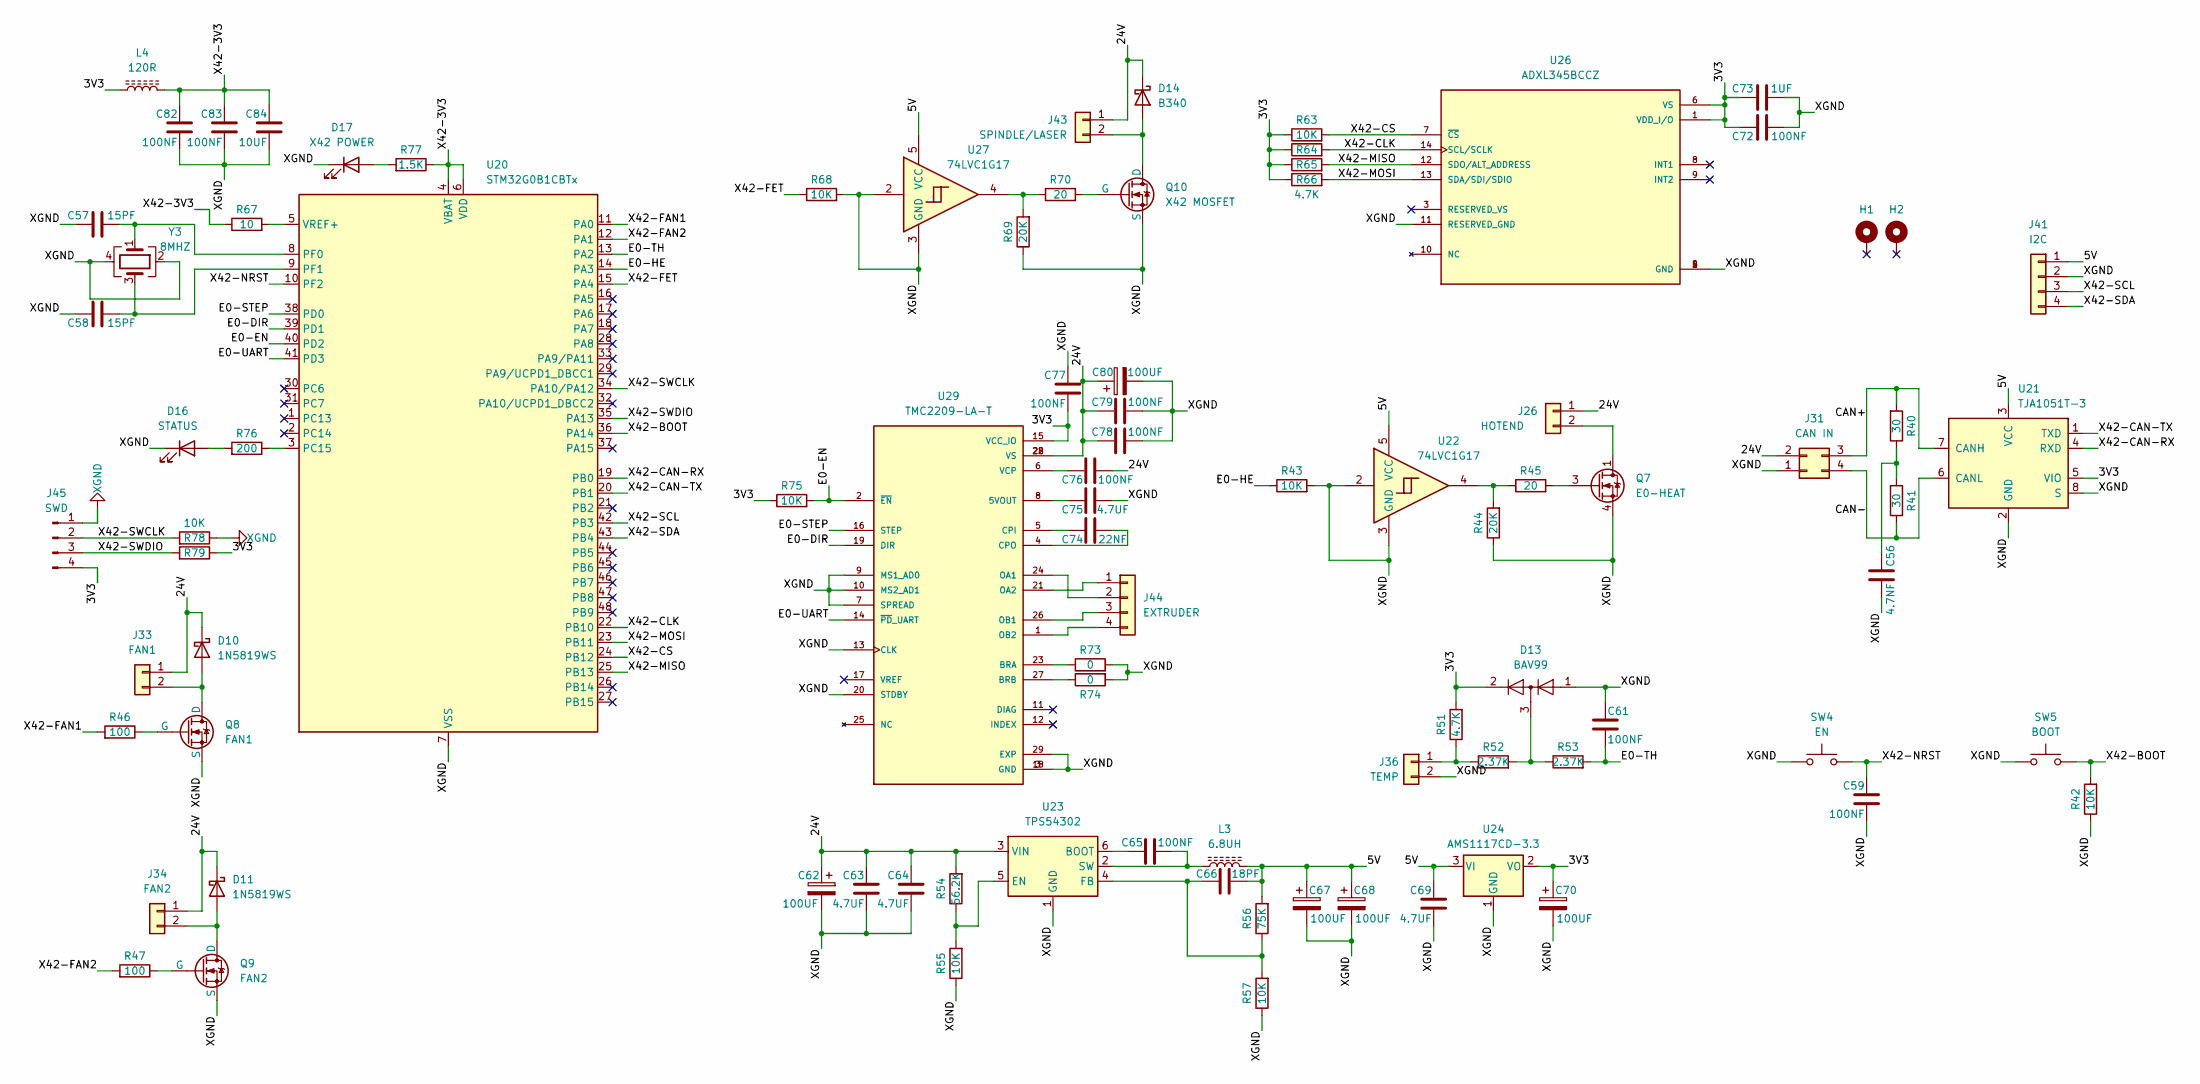
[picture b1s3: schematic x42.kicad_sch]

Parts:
C56: 4.7NF; C_0805_2012Metric
C57, C58: 15PF; C_0805_2012Metric
C59, C61, C65, C72, C76, C77, C78, C79, C82, C83: 100NF; C_0805_2012Metric
C62, C67, C68, C70, C80: 100UF; CP_Elec_5x3
C63, C64, C69, C75: 4.7UF; C_0805_2012Metric
C66: 18PF; C_0805_2012Metric
C73: 1UF; C_0805_2012Metric
C74: 22NF; C_0805_2012Metric
C84: 10UF; C_0805_2012Metric
D10, D11: 1N5819WS; D_SOD-323
D13: BAV99; SOT-23
D14: B340; D_SMC
D16: STATUS; LED_0805_2012Metric
D17: X42 POWER; LED_0805_2012Metric
H1, H2: MountingHole_Pad; MountingHole_3mm_Pad
J26: HOTEND; JST_XH_B2B-XH-A_1x02_P2.50mm_Vertical
J31: CAN IN; Molex_Micro-Fit_3.0_43045-0400_2x02_P3.00mm_Horizontal
J33: FAN1; PinHeader_1x02_P2.54mm_Vertical_SMD_Pin1Right
J34: FAN2; PinHeader_1x02_P2.54mm_Vertical_SMD_Pin1Right
J36: TEMP; JST_XH_B2B-XH-A_1x02_P2.50mm_Vertical
J41: I2C; PinHeader_1x04_P2.54mm_Vertical_SMD_Pin1Right
J43: SPINDLE/LASER; PinHeader_1x02_P2.54mm_Vertical_SMD_Pin1Right
J44: EXTRUDER; JST_XH_B4B-XH-A_1x04_P2.50mm_Vertical
J45: SWD; PinHeader_1x04_P2.54mm_Vertical_SMD_Pin1Right
L3: 6.8UH; L_6.3x6.3_H3
L4: 120R; L_0805_2012Metric
Q7: E0-HEAT; Vishay_PowerPAK_SC70-6L_Single
Q8: FAN1; SOT-23
Q9: FAN2; SOT-23
Q10: X42 MOSFET; TO-252-2
R40, R41: 30; R_0805_2012Metric
R42, R43, R55, R57, R63, R68, R75, R78, R79: 10K; R_0805_2012Metric
R44, R69: 20K; R_0805_2012Metric
R45, R70: 20; R_0805_2012Metric
R46, R47: 100; R_0805_2012Metric
R51, R64, R65, R66: 4.7K; R_0805_2012Metric
R52, R53: 2.37K; R_0805_2012Metric
R54: 56.2K; R_0805_2012Metric
R56: 75K; R_0805_2012Metric
R67: 10; R_0805_2012Metric
R73, R74: 0; R_0805_2012Metric
R76: 200; R_0805_2012Metric
R77: 1.5K; R_0805_2012Metric
SW4: EN; SW_Tactile_SPST_NO_Straight_CK_PTS636Sx25SMTRLFS
SW5: BOOT; SW_Tactile_SPST_NO_Straight_CK_PTS636Sx25SMTRLFS
U20: STM32G0B1CBTx; LQFP-48_7x7mm_P0.5mm
U21: TJA1051T-3; SOIC-8_3.9x4.9mm_P1.27mm
U22, U27: 74LVC1G17; SOT-23-5
U23: TPS54302; SOT-23-6
U24: AMS1117CD-3.3; TO-252-2
U26: ADXL345BCCZ; IC_ADXL345BCCZ; PARTREV G
U29: TMC2209-LA-T; QFN50P500X500X90-29N; PARTREV 1.09
Y3: 8MHZ; Crystal_SMD_Abracon_ABM3B-4Pin_5.0x3.2mm

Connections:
/X42/3V3: C70.1, C72.1, C73.1, C77.2, D13.2 (A), J45.4, L4.1, R51.2, R63.1, R64.1, R65.1, R66.1, R75.1, R79.1, U21.5 (VIO), U24.2 (VO), U26.1 (VDD_I/O), U26.6 (VS), U29.15 (VCC_IO)
/X42/5V: C66.1, C67.1, C68.1, C69.1, J41.1, L3.2, R56.2, U21.3 (VCC), U22.5 (VCC), U24.3 (VI), U27.5 (VCC)
/X42/24V: C62.1, C63.1, C64.1, C76.1, C78.2, C79.2, C80.1, D10.1 (K), D11.1 (K), D14.1 (K), J26.1, J31.2, J33.1, J34.1, J43.1, R54.2, U23.3 (VIN), U29.22 (VS), U29.28 (VS)
/X42/CAN+: J31.3, R40.2, U21.7 (CANH)
/X42/CAN-: J31.4, R41.1, U21.6 (CANL)
/X42/E0-DIR: U20.39 (PD1), U29.19 (DIR)
/X42/E0-EN: R75.2, U20.40 (PD2), U29.2 (~EN)
/X42/E0-HE: R43.1, U20.14 (PA3)
/X42/E0-STEP: U20.38 (PD0), U29.16 (STEP)
/X42/E0-TH: C61.2, R53.2, U20.13 (PA2)
/X42/E0-UART: U20.41 (PD3), U29.14 (~PD_UART)
/X42/X42-3V3: C82.1, C83.1, C84.1, L4.2, R67.1, R77.1, U20.4 (VBAT), U20.6 (VDD)
/X42/X42-BOOT: R42.2, SW5.2, U20.36 (PA14)
/X42/X42-CAN-RX: U20.19 (PB0), U21.4 (RXD)
/X42/X42-CAN-TX: U20.20 (PB1), U21.1 (TXD)
/X42/X42-CLK: R64.2, U20.22 (PB10), U26.14 (SCL/SCLK)
/X42/X42-CS: R63.2, U20.24 (PB12), U26.7 (~CS)
/X42/X42-FAN1: R46.2, U20.11 (PA0)
/X42/X42-FAN2: R47.2, U20.12 (PA1)
/X42/X42-FET: R68.1, U20.15 (PA4)
/X42/X42-MISO: R65.2, U20.25 (PB13), U26.12 (SDO/ALT_ADDRESS)
/X42/X42-MOSI: R66.2, U20.23 (PB11), U26.13 (SDA/SDI/SDIO)
/X42/X42-NRST: C59.1, SW4.2, U20.10 (PF2)
/X42/X42-SCL: J41.3, U20.42 (PB3)
/X42/X42-SDA: J41.4, U20.43 (PB4)
/X42/X42-SWCLK: J45.2, R78.2, U20.34 (PA10/PA12)
/X42/X42-SWDIO: J45.3, R79.2, U20.35 (PA13)
unnamed: C56.1, R40.1, R41.2
unnamed: D10.2 (A), J33.2, Q8.1 (D)
unnamed: D11.2 (A), J34.2, Q9.1 (D)
unnamed: D13.3 (K), R52.2, R53.1
unnamed: D14.2 (A), J43.2, Q10.1 (D)
unnamed: D16.2 (A), R76.2
unnamed: D17.2 (A), R77.2
unnamed: J26.2, Q7.1 (D)
unnamed: J36.1, R51.1, R52.1
unnamed: J44.1, U29.21 (OA2)
unnamed: J44.2, U29.24 (OA1)
unnamed: J44.3, U29.26 (OB1)
unnamed: J44.4, U29.1 (OB2)
unnamed: Q7.3 (G), R45.2
unnamed: Q8.2 (G), R46.1
unnamed: Q9.2 (G), R47.1
unnamed: Q10.2 (G), R70.2
unnamed: R44.2, R45.1, U22.4
unnamed: R69.2, R70.1, U27.4
unnamed: R76.1, U20.3 (PC15)
unnamed: C57.2, U20.8 (PF0), Y3.1
unnamed: C58.2, U20.9 (PF1), Y3.3
unnamed: R67.2, U20.5 (VREF+)
unnamed: C65.2, U23.6 (BOOT)
unnamed: R54.1, R55.2, U23.5 (EN)
unnamed: C66.2, R56.1, R57.2, U23.4 (FB)
unnamed: C65.1, L3.1, U23.2 (SW)
unnamed: C75.2, U29.8 (5VOUT)
unnamed: R73.1, U29.23 (BRA)
unnamed: R74.1, U29.27 (BRB)
unnamed: C74.2, U29.5 (CPI)
unnamed: C74.1, U29.4 (CPO)
unnamed: C76.2, U29.6 (VCP)
XGND: C56.2, C57.1, C58.1, C59.2, C61.1, C62.2, C63.2, C64.2, C67.2, C68.2, C69.2, C70.2, C72.2, C73.2, C75.1, C77.1, C78.1, C79.1, C80.2, C82.2, C83.2, C84.2, D13.1 (K), D16.1 (K), D17.1 (K), J31.1, J36.2, J41.2, J45.1, Q7.4 (S), Q8.3 (S), Q9.3 (S), Q10.3 (S), R42.1, R43.2, R44.1, R55.1, R57.1, R68.2, R69.1, R73.2, R74.2, R78.1, SW4.1, SW5.1, U20.7 (VSS), U21.2 (GND), U21.8 (S), U22.2, U22.3 (GND), U23.1 (GND), U24.1 (GND), U26.2 (GND), U26.4 (GND), U26.5 (GND), U26.11 (RESERVED_GND), U27.2, U27.3 (GND), U29.3 (GND), U29.7 (SPREAD), U29.9 (MS1_AD0), U29.10 (MS2_AD1), U29.13 (CLK), U29.18 (GND), U29.20 (STDBY), U29.29 (EXP), Y3.2, Y3.4
